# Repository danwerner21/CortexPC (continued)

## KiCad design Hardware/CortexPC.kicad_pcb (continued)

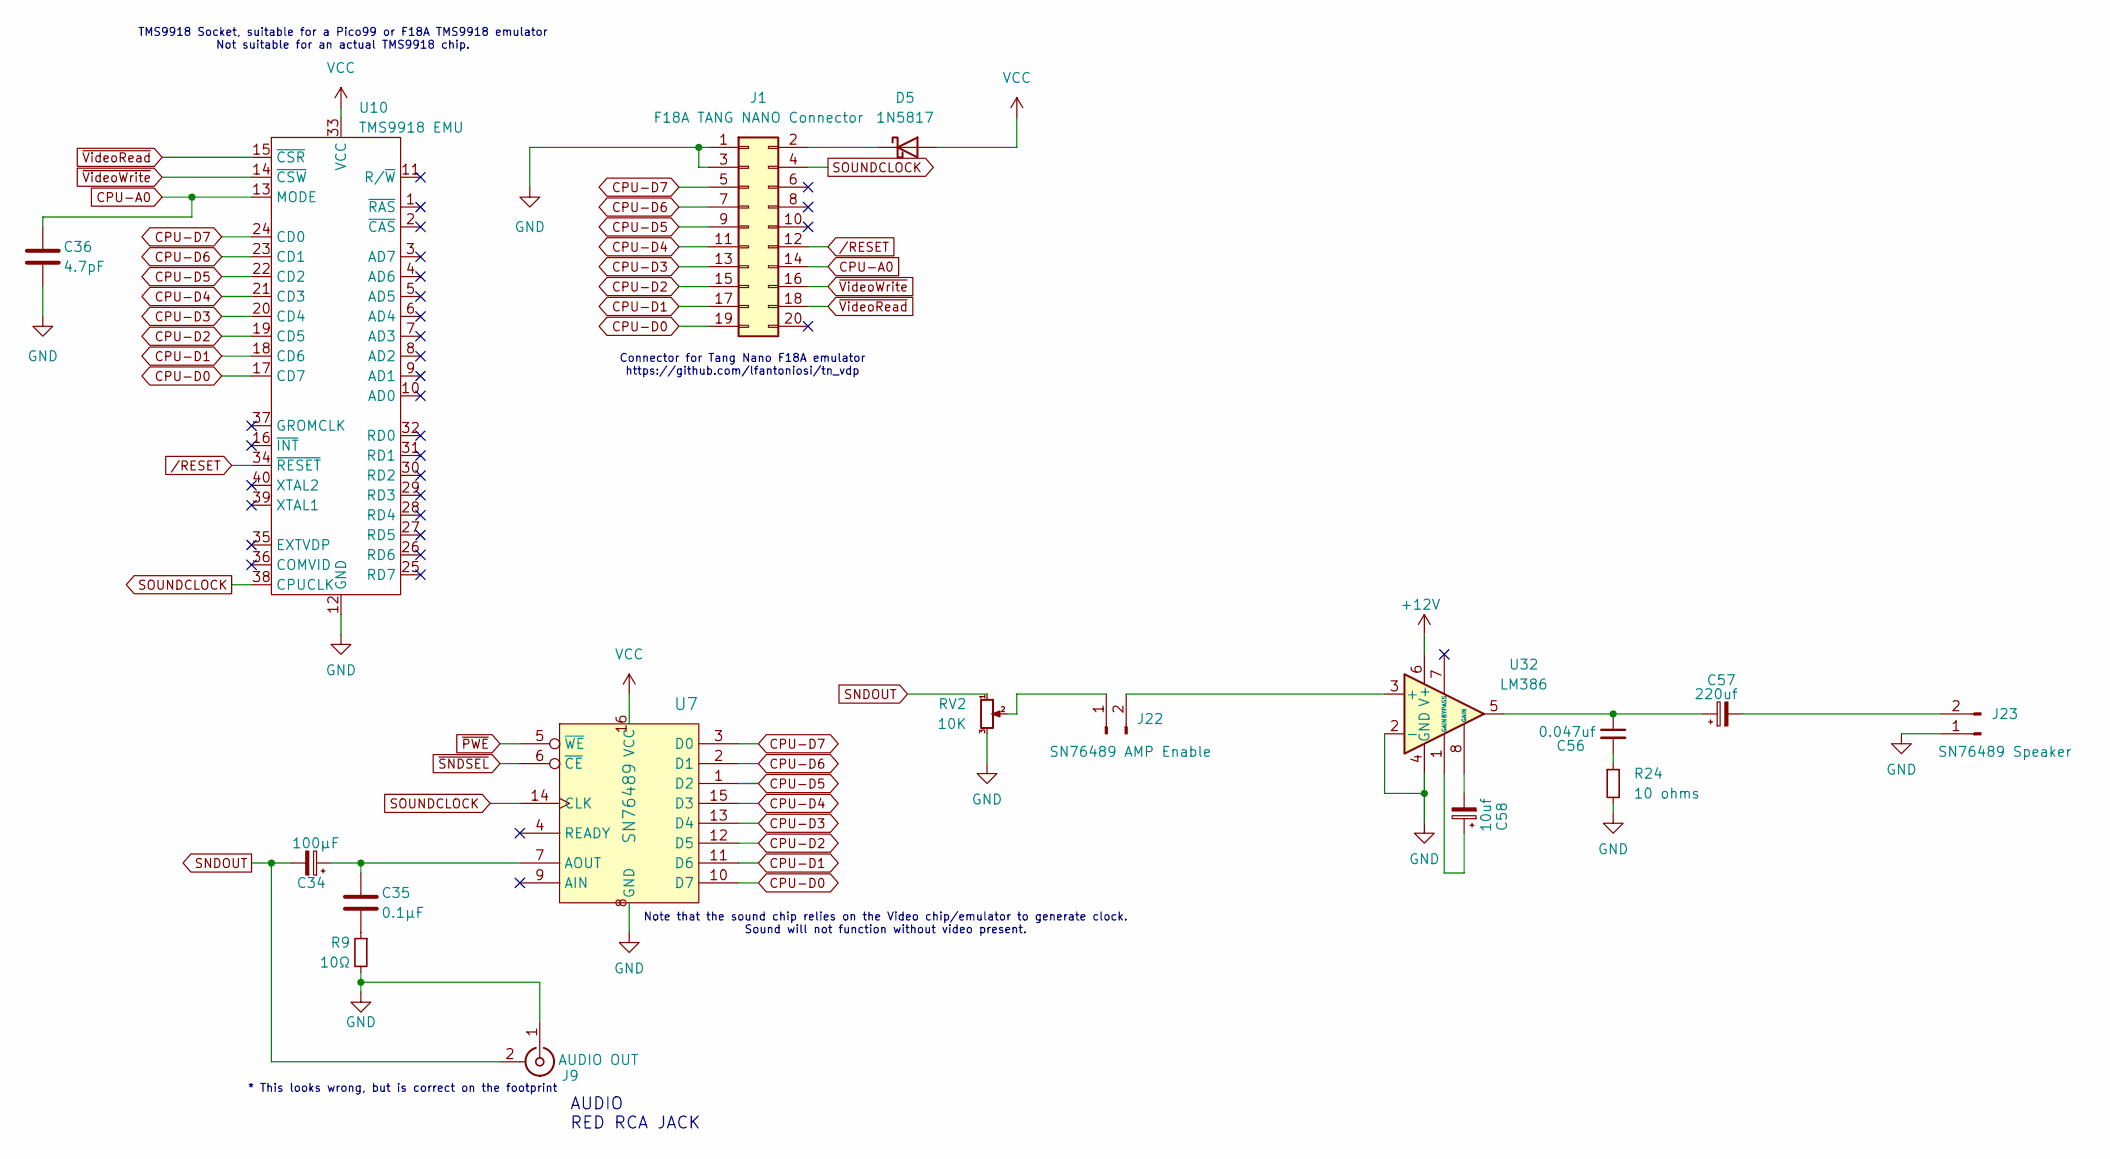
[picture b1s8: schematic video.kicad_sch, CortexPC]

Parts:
C34: 100µF; STD_DDW_PCAP
C35: 0.1µF; STD_DDW_CAP
C36: 4.7pF; STD_DDW_CAP
C56: 0.047uf; STD_DDW_CAP
C57: 220uf; STD_DDW_PCAP
C58: 10uf; STD_DDW_PCAP
D5: 1N5817; STD_DDW_DIODE
J1: F18A TANG NANO Connector; STD_DDW_PinHeader_2x10
J9: AUDIO OUT; CUI_RCJ-047
J22: SN76489 AMP Enable; STD_DDW_PINHEAD_V_1x02
J23: SN76489 Speaker; STD_DDW_PINHEAD_V_1x02
R9: 10Ω; STD_DDW_RESISTOR
R24: 10 ohms; STD_DDW_RESISTOR
RV2: 10K; Potentiometer_Bourns_3386F_Vertical
U7: SN76489; STD_DDW_DIP16
U10: TMS9918 EMU; STD_DDW_DIP40
U32: LM386; STD_DDW_DIP8

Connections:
+12V: U32.6 (V+); also elsewhere on the board
CPU-A0: C36.1, J1.14, U10.13 (MODE); also elsewhere on the board
CPU-D0: J1.19, U7.10 (D7), U10.17 (CD7); also elsewhere on the board
CPU-D1: J1.17, U7.11 (D6), U10.18 (CD6); also elsewhere on the board
CPU-D2: J1.15, U7.12 (D5), U10.19 (CD5); also elsewhere on the board
CPU-D3: J1.13, U7.13 (D4), U10.20 (CD4); also elsewhere on the board
CPU-D4: J1.11, U7.15 (D3), U10.21 (CD3); also elsewhere on the board
CPU-D5: J1.9, U7.1 (D2), U10.22 (CD2); also elsewhere on the board
CPU-D6: J1.7, U7.2 (D1), U10.23 (CD1); also elsewhere on the board
CPU-D7: J1.5, U7.3 (D0), U10.24 (CD0); also elsewhere on the board
GND: C36.2, J1.1, J1.3, J9.1 (In), J23.1, R9.2, R24.2, RV2.3, U7.8 (GND), U10.12 (GND), U32.2 (-), U32.4 (GND); also elsewhere on the board
unnamed: C35.2, R9.1
unnamed: C56.1, C57.1, U32.5
unnamed: C56.2, R24.1
unnamed: C58.1, U32.1 (GAIN)
unnamed: C58.2, U32.8 (GAIN)
unnamed: D5.1 (K), J1.2
unnamed: J22.1, RV2.2
unnamed: J22.2, U32.3 (+)
unnamed: C57.2, J23.2
unnamed: C34.1, C35.1, U7.7 (AOUT)
SNDOUT: C34.2, J9.2 (Ext), RV2.1
SOUNDCLOCK: J1.4, U7.14 (CLK), U10.38 (CPUCLK)
VCC: D5.2 (A), U7.16 (VCC), U10.33 (VCC); also elsewhere on the board
/RESET: J1.12, U10.34 (~RESET); also elsewhere on the board
~PWE: U7.5 (~WE); also elsewhere on the board
~SNDSEL: U7.6 (~CE); also elsewhere on the board
~VideoRead: J1.18, U10.15 (~CSR); also elsewhere on the board
~VideoWrite: J1.16, U10.14 (~CSW); also elsewhere on the board

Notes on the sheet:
AUDIO RED RCA JACK
Connector for Tang Nano F18A emulator https://github.com/lfantoniosi/tn_vdp
* This looks wrong, but is correct on the footprint
Note that the sound chip relies on the Video chip/emulator to generate clock. Sound will not function without video present.
TMS9918 Socket, suitable for a Pico99 or F18A TMS9918 emulator Not suitable for an actual TMS9918 chip.

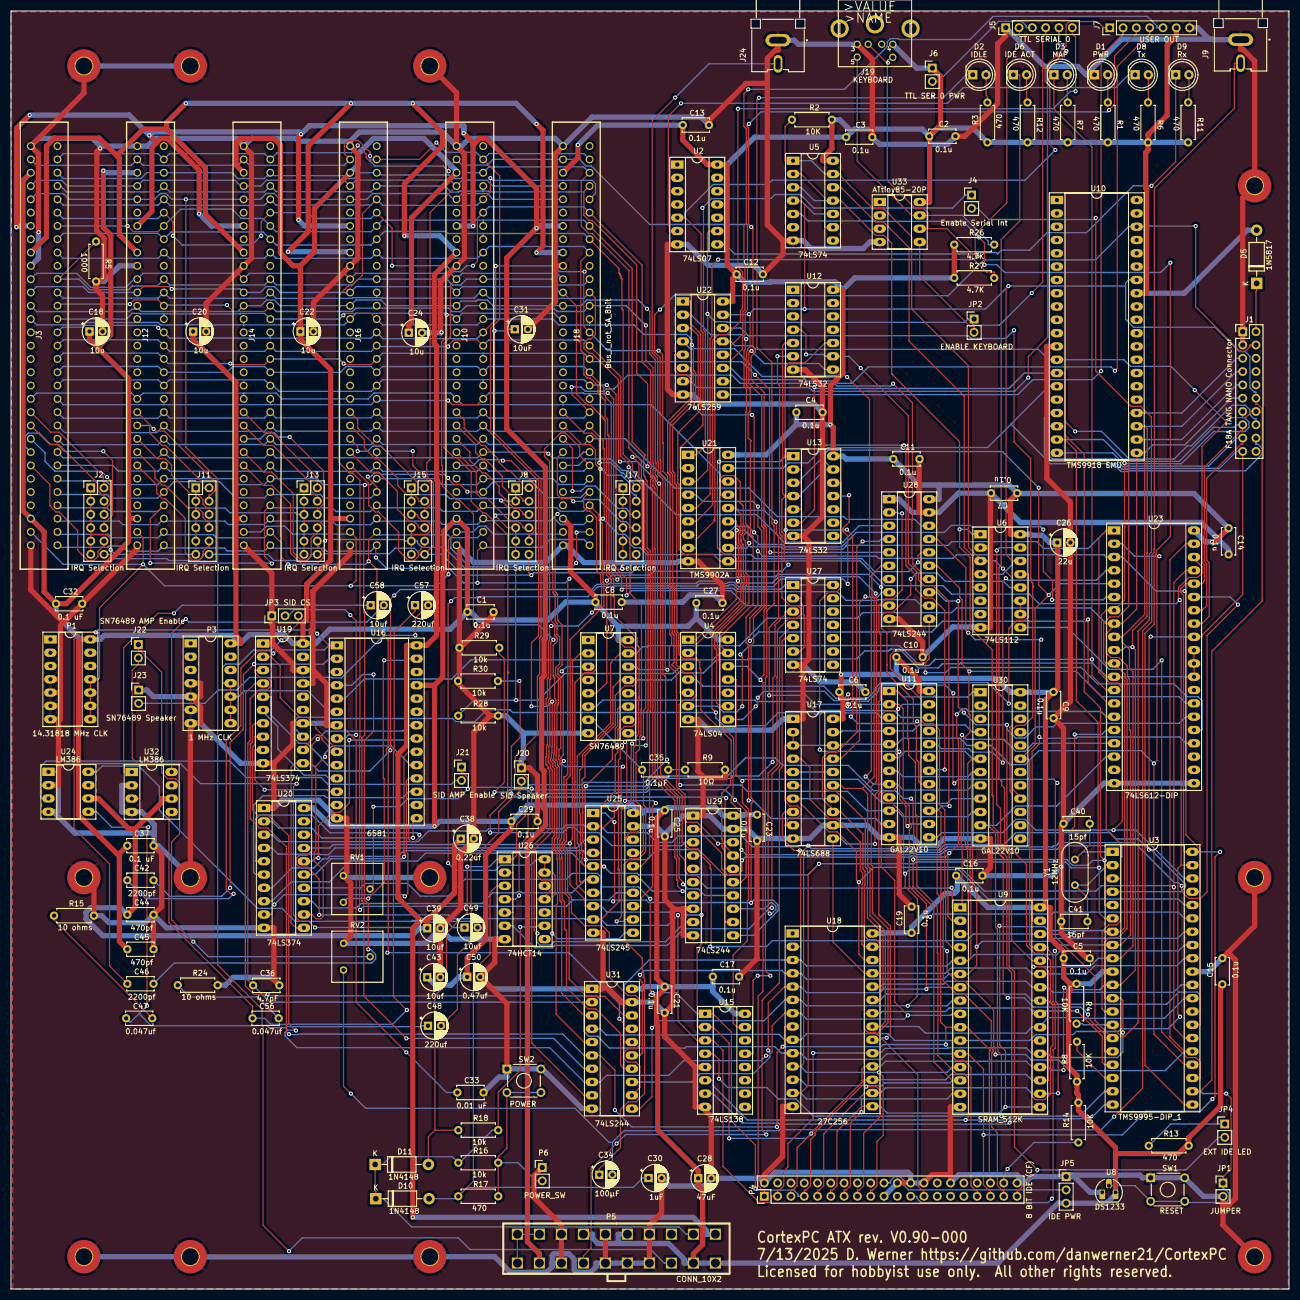
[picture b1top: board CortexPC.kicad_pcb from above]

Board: 2 copper layers, 244.0 x 244.0 mm, 167 parts (0 on the bottom side), 226 nets.

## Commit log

2025-06-09 update with SID
2025-07-14 notes
2025-07-20 cortex work
2025-08-09 Cortex Updates
2025-08-11 rom source updates
2025-08-11 rom work
2025-12-12 add new software
